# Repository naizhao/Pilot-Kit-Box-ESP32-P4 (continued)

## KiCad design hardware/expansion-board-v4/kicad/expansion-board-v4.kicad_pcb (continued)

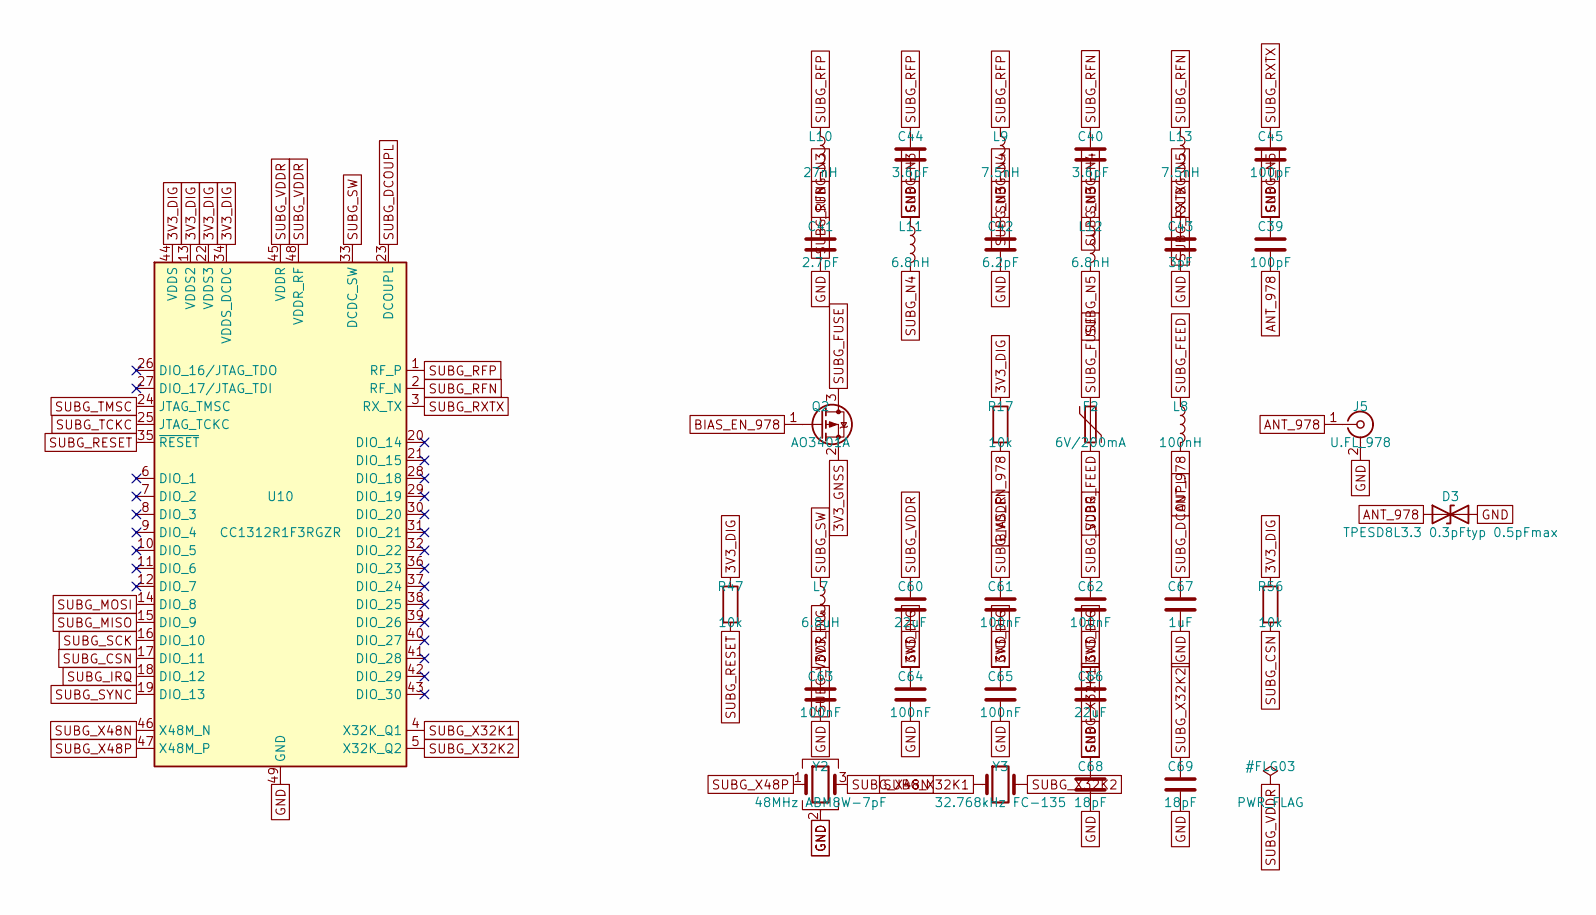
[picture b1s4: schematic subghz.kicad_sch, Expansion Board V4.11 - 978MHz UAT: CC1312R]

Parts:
C39, C45: 100pF; C_0402_1005Metric
C40, C44: 3.6pF; C_0402_1005Metric
C41: 2.7pF; C_0402_1005Metric
C42: 6.2pF; C_0402_1005Metric
C43: 3pF; C_0402_1005Metric
C60, C66: 22uF; C_0805_2012Metric
C61, C62, C63, C64, C65: 100nF; C_0603_1608Metric
C67: 1uF; C_0603_1608Metric
C68, C69: 18pF; C_0603_1608Metric
D3: TPESD8L3.3 0.3pFtyp 0.5pFmax; D_0402_1005Metric
F2: 6V/200mA; Fuse_0805_2012Metric
J5: U.FL_978; U.FL_Hirose_U.FL-R-SMT-1_Vertical
L7: 6.8uH; L_0805_2012Metric
L8: 100nH; L_0402_1005Metric
L9, L13: 7.5nH; L_0402_1005Metric
L10: 27nH; L_0402_1005Metric
L11, L12: 6.8nH; L_0402_1005Metric
Q2: AO3401A; SOT-23
R17, R47, R56: 10k; R_0603_1608Metric
U10: CC1312R1F3RGZR; QFN-48-1EP_7x7mm_P0.5mm_EP5.15x5.15mm
Y2: 48MHz ABM8W-7pF; Crystal_SMD_3225-4Pin_3.2x2.5mm
Y3: 32.768kHz FC-135; Crystal_SMD_3215-2Pin_3.2x1.5mm

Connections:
3V3_DIG: C63.1, C64.1, C65.1, C66.1, R17.1, R47.1, R56.1, U10.13 (VDDS2), U10.22 (VDDS3), U10.34 (VDDS_DCDC), U10.44 (VDDS); also elsewhere on the board
3V3_GNSS: Q2.2 (S); also elsewhere on the board
ANT_978: C39.2, D3.1 (A1), J5.1 (In), L8.2
BIAS_EN_978: Q2.1 (G), R17.2; also elsewhere on the board
GND: C41.2, C42.2, C43.2, C44.2, C45.2, C60.2, C61.2, C62.2, C63.2, C64.2, C65.2, C66.2, C67.2, C68.2, C69.2, D3.2 (A2), J5.2 (Ext), U10.49 (GND), Y2.2 (G), Y2.4 (G); also elsewhere on the board
SUBG_CSN: R56.2, U10.17 (DIO_11); also elsewhere on the board
SUBG_DCOUPL: C67.1, U10.23 (DCOUPL)
SUBG_FEED: F2.2, L8.1
SUBG_FUSE: F2.1, Q2.3 (D)
SUBG_IRQ: U10.18 (DIO_12); also elsewhere on the board
SUBG_MISO: U10.15 (DIO_9); also elsewhere on the board
SUBG_MOSI: U10.14 (DIO_8); also elsewhere on the board
SUBG_N3: C40.2, C41.1, L9.2, L11.1
SUBG_N4: C42.1, L11.2, L12.1
SUBG_N5: C39.1, C43.1, L12.2
SUBG_RESET: R47.2, U10.35 (~RESET); also elsewhere on the board
SUBG_RFN: C40.1, L10.2, L13.1, U10.2 (RF_N)
SUBG_RFP: C44.1, L9.1, L10.1, U10.1 (RF_P)
SUBG_RXTX: C45.1, L13.2, U10.3 (RX_TX)
SUBG_SCK: U10.16 (DIO_10); also elsewhere on the board
SUBG_SW: L7.1, U10.33 (DCDC_SW)
SUBG_SYNC: U10.19 (DIO_13); also elsewhere on the board
SUBG_TCKC: U10.25 (JTAG_TCKC); also elsewhere on the board
SUBG_TMSC: U10.24 (JTAG_TMSC); also elsewhere on the board
SUBG_VDDR: C60.1, C61.1, C62.1, L7.2, U10.45 (VDDR), U10.48 (VDDR_RF)
SUBG_X32K1: C68.1, U10.4 (X32K_Q1), Y3.1
SUBG_X32K2: C69.1, U10.5 (X32K_Q2), Y3.2
SUBG_X48N: U10.46 (X48M_N), Y2.3
SUBG_X48P: U10.47 (X48M_P), Y2.1

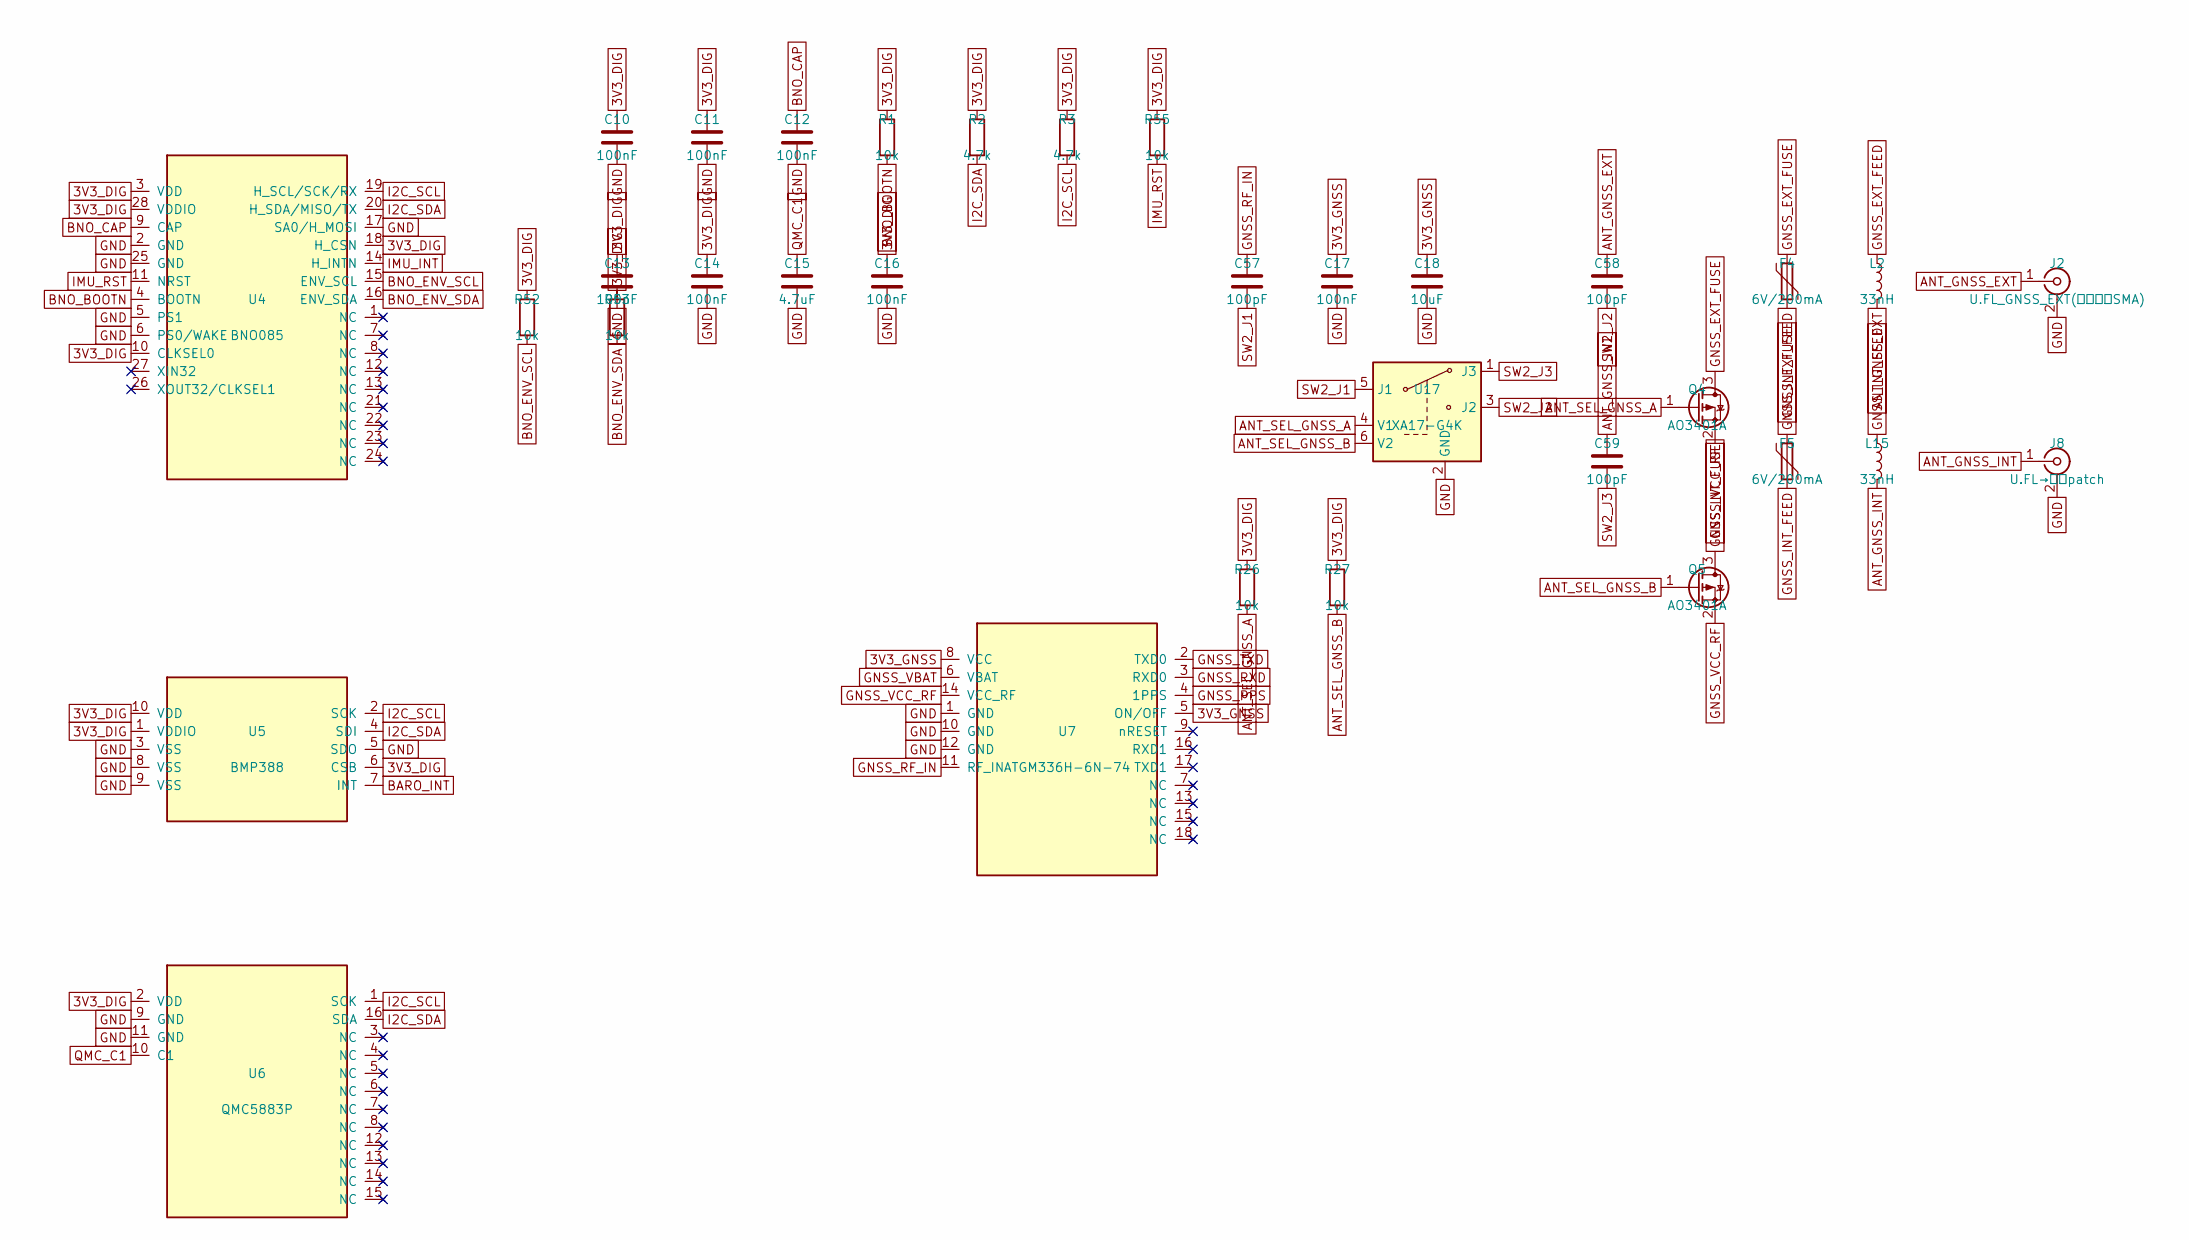
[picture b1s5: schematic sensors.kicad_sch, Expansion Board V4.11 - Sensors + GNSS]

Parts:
C10, C11, C12, C13, C14, C16, C17: 100nF; C_0603_1608Metric
C15: 4.7uF; C_0603_1608Metric
C18: 10uF; C_0805_2012Metric
C57, C58, C59: 100pF; C_0402_1005Metric
F4, F5: 6V/200mA; Fuse_0805_2012Metric
J2: U.FL_GNSS_EXT(经尾线转SMA); U.FL_Hirose_U.FL-R-SMT-1_Vertical
J8: U.FL→内置patch; U.FL_Hirose_U.FL-R-SMT-1_Vertical
L2, L15: 33nH; L_0402_1005Metric
Q4, Q5: AO3401A; SOT-23
R1, R26, R27, R55: 10k; R_0603_1608Metric
R2, R3: 4.7k; R_0603_1608Metric
R52, R53: 10k; R_0402_1005Metric
U4: BNO085; BNO085_LGA-28
U5: BMP388; BMP388_LGA-10
U6: QMC5883P; LGA-16_3x3mm_P0.5mm
U7: ATGM336H-6N-74; ATGM336H_LCC-18
U17: XA17-G4K; SOT-363_SC-70-6

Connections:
3V3_DIG: C10.1, C11.1, C13.1, C14.1, C16.1, R1.1, R2.1, R3.1, R26.1, R27.1, R52.1, R53.1, R55.1, U4.3 (VDD), U4.10 (CLKSEL0), U4.18 (H_CSN), U4.28 (VDDIO), U5.1 (VDDIO), U5.6 (CSB), U5.10 (VDD), U6.2 (VDD); also elsewhere on the board
3V3_GNSS: C17.1, C18.1, U7.5 (ON/OFF), U7.8 (VCC); also elsewhere on the board
ANT_GNSS_EXT: C58.1, J2.1 (In), L2.2
ANT_GNSS_INT: C59.1, J8.1 (In), L15.2
ANT_SEL_GNSS_A: Q4.1 (G), R26.2, U17.4 (V1); also elsewhere on the board
ANT_SEL_GNSS_B: Q5.1 (G), R27.2, U17.6 (V2); also elsewhere on the board
BARO_INT: U5.7 (INT); also elsewhere on the board
BNO_BOOTN: R1.2, U4.4 (BOOTN)
BNO_CAP: C12.1, U4.9 (CAP)
BNO_ENV_SCL: R52.2, U4.15 (ENV_SCL)
BNO_ENV_SDA: R53.2, U4.16 (ENV_SDA)
GND: C10.2, C11.2, C12.2, C13.2, C14.2, C15.2, C16.2, C17.2, C18.2, J2.2 (Ext), J8.2 (Ext), U4.2 (GND), U4.5 (PS1), U4.6 (PS0/WAKE), U4.17 (SA0/H_MOSI), U4.25 (GND), U5.3 (VSS), U5.5 (SDO), U5.8 (VSS), U5.9 (VSS), U6.9 (GND), U6.11 (GND), U7.1 (GND), U7.10 (GND), U7.12 (GND), U17.2 (GND); also elsewhere on the board
GNSS_EXT_FEED: F4.2, L2.1
GNSS_EXT_FUSE: F4.1, Q4.3 (D)
GNSS_INT_FEED: F5.2, L15.1
GNSS_INT_FUSE: F5.1, Q5.3 (D)
GNSS_PPS: U7.4 (1PPS); also elsewhere on the board
GNSS_RF_IN: C57.1, U7.11 (RF_IN)
GNSS_RXD: U7.3 (RXD0); also elsewhere on the board
GNSS_TXD: U7.2 (TXD0); also elsewhere on the board
GNSS_VBAT: U7.6 (VBAT); also elsewhere on the board
GNSS_VCC_RF: Q4.2 (S), Q5.2 (S), U7.14 (VCC_RF)
I2C_SCL: R3.2, U4.19 (H_SCL/SCK/RX), U5.2 (SCK), U6.1 (SCK); also elsewhere on the board
I2C_SDA: R2.2, U4.20 (H_SDA/MISO/TX), U5.4 (SDI), U6.16 (SDA); also elsewhere on the board
IMU_INT: U4.14 (H_INTN); also elsewhere on the board
IMU_RST: R55.2, U4.11 (NRST); also elsewhere on the board
QMC_C1: C15.1, U6.10 (C1)
SW2_J1: C57.2, U17.5 (J1)
SW2_J2: C58.2, U17.3 (J2)
SW2_J3: C59.2, U17.1 (J3)

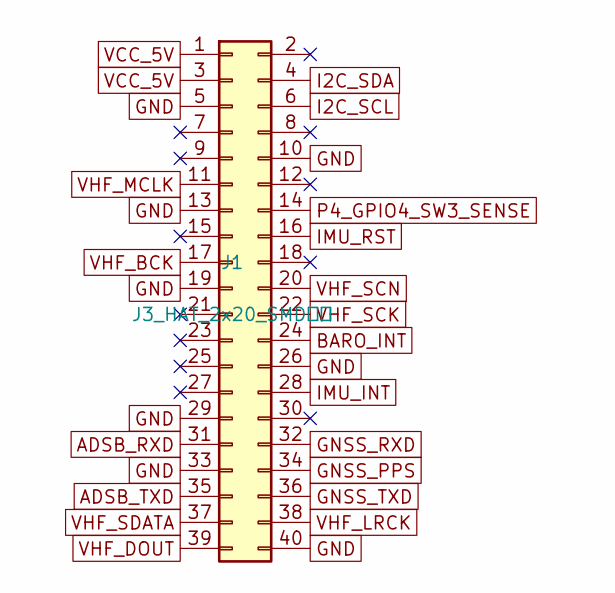
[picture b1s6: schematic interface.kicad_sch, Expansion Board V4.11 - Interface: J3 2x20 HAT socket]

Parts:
J1: J3_HAT_2x20_SMD排针; PinHeader_2x20_P2.54mm_Vertical_SMD

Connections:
ADSB_RXD: J1.31; also elsewhere on the board
ADSB_TXD: J1.35; also elsewhere on the board
BARO_INT: J1.24; also elsewhere on the board
GND: J1.5, J1.10, J1.13, J1.19, J1.26, J1.29, J1.33, J1.40; also elsewhere on the board
GNSS_PPS: J1.34; also elsewhere on the board
GNSS_RXD: J1.32; also elsewhere on the board
GNSS_TXD: J1.36; also elsewhere on the board
I2C_SCL: J1.6; also elsewhere on the board
I2C_SDA: J1.4; also elsewhere on the board
IMU_INT: J1.28; also elsewhere on the board
IMU_RST: J1.16; also elsewhere on the board
P4_GPIO4_SW3_SENSE: J1.14; also elsewhere on the board
VCC_5V: J1.1, J1.3; also elsewhere on the board
VHF_BCK: J1.17; also elsewhere on the board
VHF_DOUT: J1.39; also elsewhere on the board
VHF_LRCK: J1.38; also elsewhere on the board
VHF_MCLK: J1.11; also elsewhere on the board
VHF_SCK: J1.22; also elsewhere on the board
VHF_SCN: J1.20; also elsewhere on the board
VHF_SDATA: J1.37; also elsewhere on the board

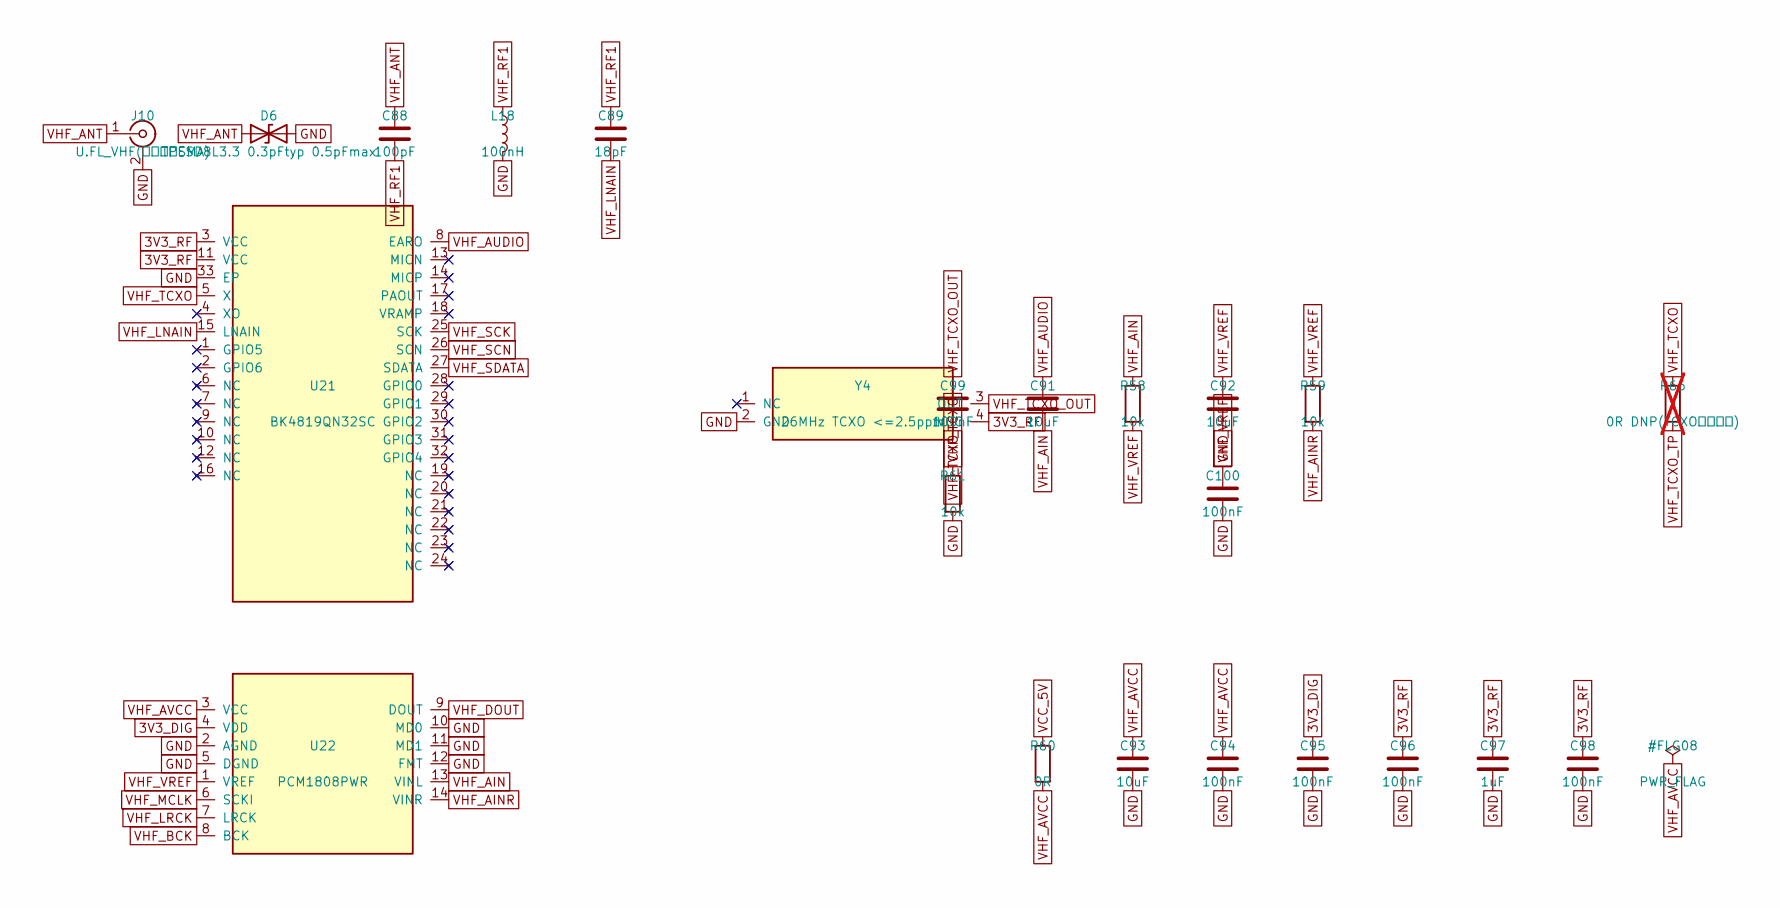
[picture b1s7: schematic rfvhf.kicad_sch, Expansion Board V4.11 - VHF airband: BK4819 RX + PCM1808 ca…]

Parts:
C88: 100pF; C_0603_1608Metric
C89: 18pF; C_0603_1608Metric
C91, C92, C93: 10uF; C_0805_2012Metric
C94, C95, C96, C98, C100: 100nF; C_0603_1608Metric
C97: 1uF; C_0603_1608Metric
C99: 100nF; C_0402_1005Metric
D6: TPESD8L3.3 0.3pFtyp 0.5pFmax; D_0402_1005Metric
J10: U.FL_VHF(经尾线转SMA); U.FL_Hirose_U.FL-R-SMT-1_Vertical
L18: 100nH; L_0402_1005Metric
R58, R59: 10k; R_0603_1608Metric
R60: 0R; R_0603_1608Metric
R61: 10k; R_0402_1005Metric
R66: 0R DNP(TCXO探测隔离); R_0603_1608Metric; not fitted
U21: BK4819QN32SC; QFN-32-1EP_4x4mm_P0.4mm_EP2.65x2.65mm
U22: PCM1808PWR; TSSOP-14_4.4x5mm_P0.65mm
Y4: 26MHz TCXO <=2.5ppm; Crystal_SMD_2520-4Pin_2.5x2.0mm

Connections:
3V3_DIG: C95.1, U22.4 (VDD); also elsewhere on the board
3V3_RF: C96.1, C97.1, C98.1, U21.3 (VCC), U21.11 (VCC), Y4.4 (VCC); also elsewhere on the board
GND: C92.2, C93.2, C94.2, C95.2, C96.2, C97.2, C98.2, C100.2, D6.2 (A2), J10.2 (Ext), L18.2, R61.2, U21.33 (EP), U22.2 (AGND), U22.5 (DGND), U22.10 (MD0), U22.11 (MD1), U22.12 (FMT), Y4.2 (GND); also elsewhere on the board
VCC_5V: R60.1; also elsewhere on the board
VHF_AIN: C91.2, R58.1, U22.13 (VINL)
VHF_AINR: R59.2, U22.14 (VINR)
VHF_ANT: C88.1, D6.1 (A1), J10.1 (In)
VHF_AUDIO: C91.1, U21.8 (EARO); also elsewhere on the board
VHF_AVCC: C93.1, C94.1, R60.2, U22.3 (VCC)
VHF_BCK: U22.8 (BCK); also elsewhere on the board
VHF_DOUT: U22.9 (DOUT); also elsewhere on the board
VHF_LNAIN: C89.2, U21.15 (LNAIN)
VHF_LRCK: U22.7 (LRCK); also elsewhere on the board
VHF_MCLK: U22.6 (SCKI); also elsewhere on the board
VHF_RF1: C88.2, C89.1, L18.1
VHF_SCK: U21.25 (SCK); also elsewhere on the board
VHF_SCN: U21.26 (SCN); also elsewhere on the board
VHF_SDATA: U21.27 (SDATA); also elsewhere on the board
VHF_TCXO: C99.2, R61.1, R66.1, U21.5 (XI)
VHF_TCXO_OUT: C99.1, Y4.3 (OUT)
VHF_TCXO_TP: R66.2; also elsewhere on the board
VHF_VREF: C92.1, C100.1, R58.2, R59.1, U22.1 (VREF)

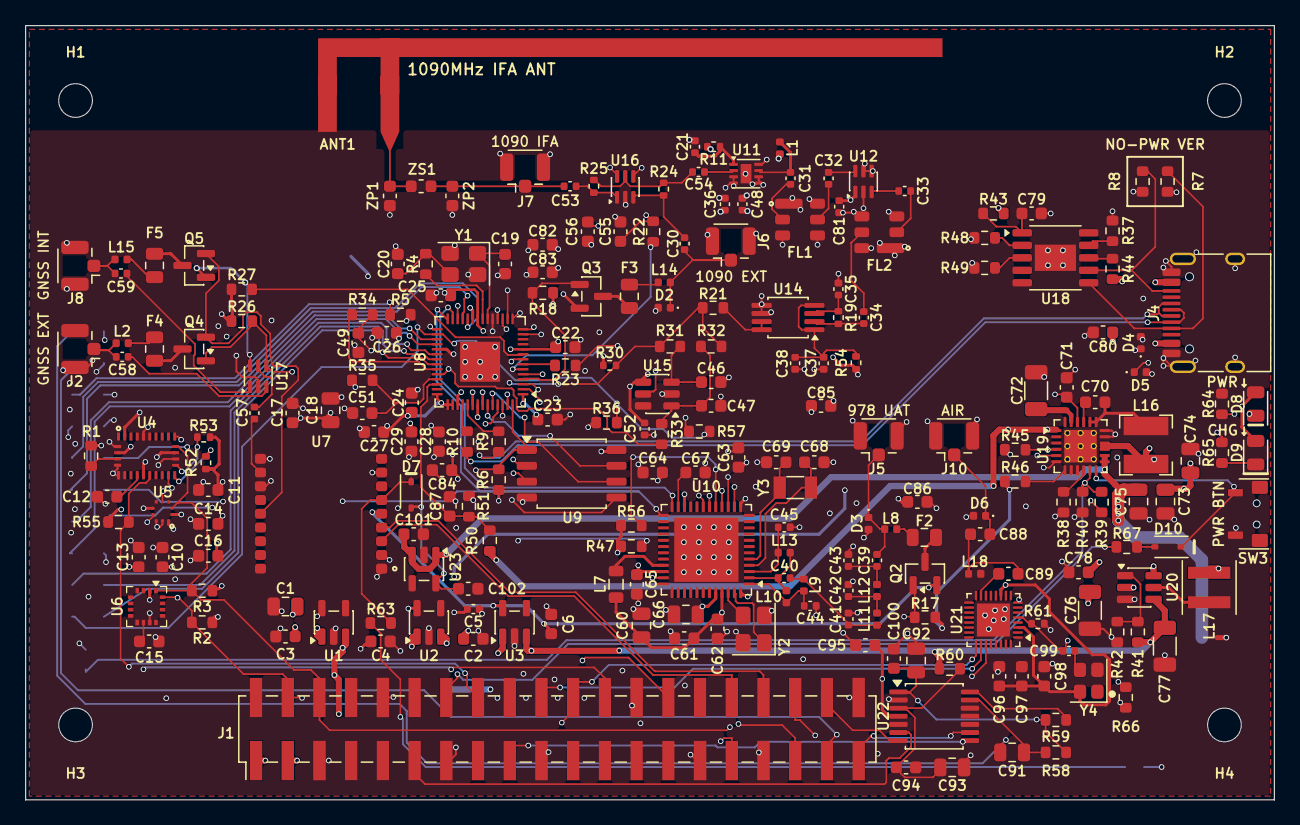
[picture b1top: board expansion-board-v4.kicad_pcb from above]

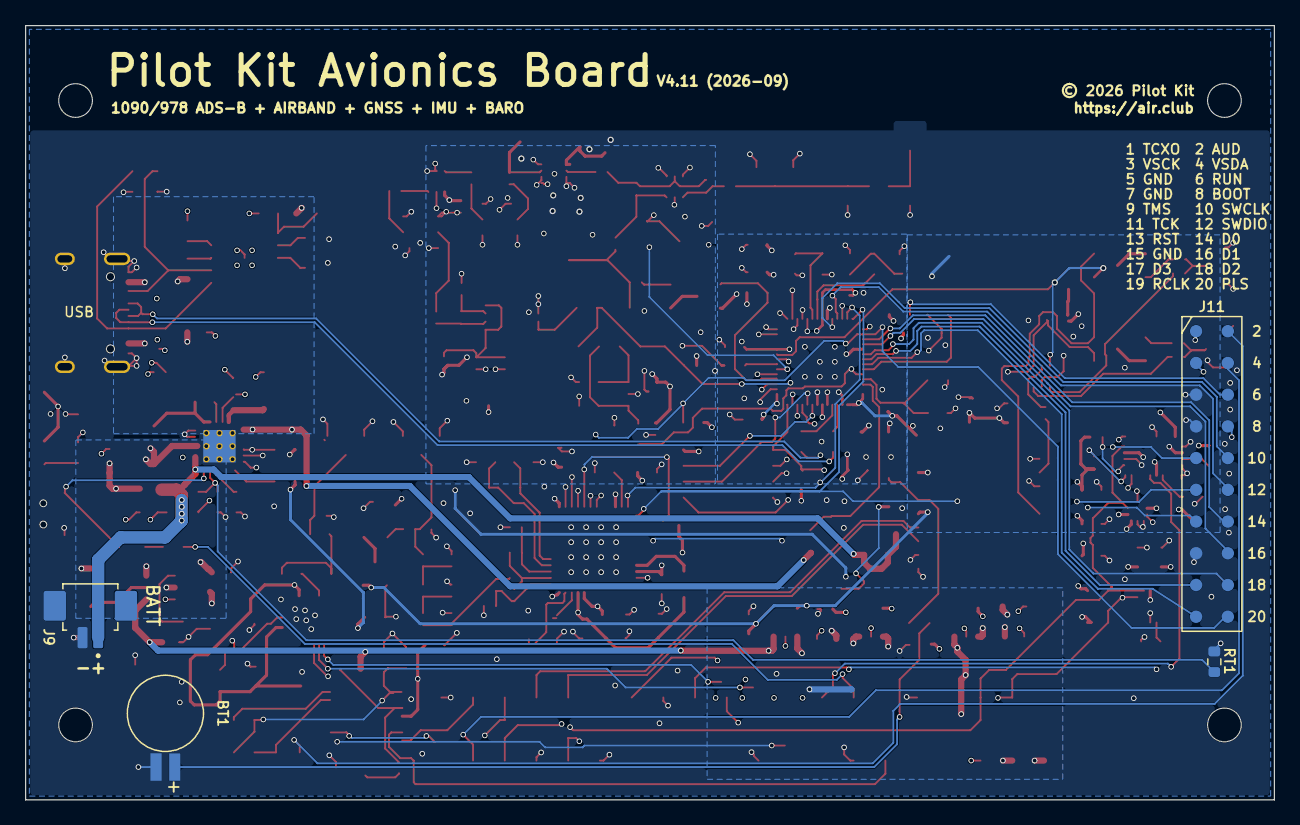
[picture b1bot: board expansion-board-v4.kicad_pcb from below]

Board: 6 copper layers, 100.0 x 62.0 mm, 235 parts (4 on the bottom side), 162 nets.

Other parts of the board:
H1, H2, H3, H4: MountingHole_2.7mm_M2.5

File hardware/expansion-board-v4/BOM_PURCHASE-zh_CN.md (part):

# V4.11 采购清单（唯一权威版，从网表自动导出——不要手改）

> ⚠️ **本文件取代此前散落在设计文档 §7/§12/§13 的所有采购表格。**

> 网表变更后重跑 `gen_bom.py` 即可；脚本带断言，任何未归类的元件都会报错，不会漏项。

> **IFA**：50.0mm铜箔外包络（48.5mm中心线）已按V4.0实板装盒VNA结果定型；默认0R/DNP为本次实测直通状态。


共 231 个元件 / 106 个料号。


**库类型**：`基础✅` 免 ¥20 上机费且损耗由嘉立创承担；`扩展⚠️` 每种 ¥20（当前靠券减免，券没了就是真金白银）。本轮在用的扩展库料共 **27 种**，下次优化优先从这些里找基础库替代。`按值配料` 表示没指定料号，库类型由嘉立创匹配页当场决定——那些也要在匹配时留意。


| 采购 | 类别 | 值/规格 | 封装 | 数量 | 位号 | 推荐型号 | 立创料号 | 库 | 说明 |
|---|---|---|---|---|---|---|---|---|---|
| 🔴必买指定 | 二极管 | 1N4148WS | D_SOD-323 | 2 | D10,D7 | 1N4148WS | C2128 | ? | 3V3_BKP → GNSS_VBAT 隔离：挡住主电池放空后电池经 LDO 输出倒灌回输入（TPS7A20 手册明确会损坏器件）；基础库 |
| 🔴必买指定 | 低电容ESD | TPESD8L3.3 0.3pFtyp 0.5pFmax | D_0402_1005Metric | 5 | D2,D3,D4,D5,D6 | TECH PUBLIC TPESD8L3.3CT5G | C2830293 | 扩展⚠️ | D2/D3 天线口 + D4/D5 USB D+/D−，同一料号。Cj 0.3pF typ / 0.5pF max（TPESD8L3.3_OCR.pdf 实测表）；普通 5V ESD 管 Cj 20-50pF 会直接吃掉射频信号。双向、无极性 |
| 🔴必买指定 | 备份电池 | MS621FE-FL11E(选贴) | MS621FE-FL11E | 1 | BT1 | Seiko MS621FE-FL11E | 淘宝（嘉立创无此料） | ? | 3V 可充电锂锰 5.5mAh φ6.8×2.1 焊接式；⚠️只能用 ML/MS 体系，LIR 满电 4.2V 会超 GNSS VBAT 的 3.6V 极限。封装自建（官方 FL11E 焊脚中心距 2.5mm，KiCad 官方库那个是 1.5mm，对不上）。手焊，不进 SMT |
| 🔴必买指定 | 射频-978匹配 | 2.7pF | C_0402_1005Metric | 1 | C41 | 风华 0402CG2R7C500NT（C0G） | C1561 | 扩展⚠️ | ⚠️必须 C0G |
| 🔴必买指定 | 射频-978匹配 | 27nH | L_0402_1005Metric | 1 | L10 | muRata LQW15AN27NH00D（绕线 ±3% SRF3.5G） | C113111 | 扩展⚠️ | 备选 Sunltech SCW1005C27NJST C330864（±5% SRF3.5G 库存8872）、APV AHW1005C-27NJTF C6364690（±5% SRF2.48G） |
| 🔴必买指定 | 射频-978匹配 | 3.6pF | C_0402_1005Metric | 2 | C40,C44 | YAGEO AC0402CRNPO9BN3R6（C0G） | C5552081 | 扩展⚠️ | ⚠️必须 C0G/NP0，X7R 调不准匹配 |
| 🔴必买指定 | 射频-978匹配 | 6.2pF | C_0402_1005Metric | 1 | C42 | 风华 0402CG6R2C500NT（C0G） | C41744 | 扩展⚠️ | ⚠️必须 C0G |
| 🔴必买指定 | 射频-978匹配 | 6.8nH | L_0402_1005Metric | 2 | L11,L12 | muRata LQW15AN6N8G00D（绕线高Q） | C82919 | 扩展⚠️ | 国产替代 Sunltech SCW1005C6N8JST C330847 |
| 🔴必买指定 | 射频-978匹配 | 7.5nH | L_0402_1005Metric | 2 | L13,L9 | muRata LQW15AN7N5G00D（绕线高Q） | C82918 | 扩展⚠️ | 国产替代 Sunltech SCW1005C7N5JST C330848 |
| 🔴必买指定 | 射频-LNA偏置 | 3.32k | R_0402_1005Metric | 1 | R11 | 0402 3.32k ±1% | — | 按值配料 | QPL9547 pin1 Vbias；按原厂评估板值，禁止用 0Ω 直连 3V3_RF |
| 🔴必买指定 | 射频-LNA去耦 | 470pF C0G | C_0402_1005Metric | 1 | C81 | 0402 470pF C0G/NP0 ±5% | — | 按值配料 | BGA2817 pin1 专属 Cdec；贴近 U12，替代料必须锁 C0G/NP0 |
| 🔴必买指定 | 射频-LNA馈电扼流 | 18nH 0402CS-18NXGRW | L_0402_1005Metric | 1 | L1 | Coilcraft 0402CS-18NXGRW 或同等高 SRF 绕线 18nH | — | 按值配料 | QPL9547 pin7 漏极馈电；按原厂评估板 18nH，替代料必须核对 1090MHz 时仍为感性 |
| 🔴必买指定 | 射频-偏置扼流 | 100nH | L_0402_1005Metric | 3 | L14,L18,L8 | DDY WI0402IFR10KST-HF（绕线） | C18221115 | 扩展⚠️ | ⚠️SRF 1.4GHz。常见的叠层款 SRF 仅 600-700MHz，在 1090MHz 已变电容会把射频短到电源 |
| 🔴必买指定 | 射频-偏置扼流 | 33nH | L_0402_1005Metric | 2 | L15,L2 | APV AHW1005C-33NJTF（绕线） | C6807986 | 扩展⚠️ | ⚠️SRF 2.35GHz。GNSS 1575MHz 要求 SRF≥2GHz，叠层款不合格 |
| 🔴必买指定 | 射频-检波耦合 | 3pF | C_0402_1005Metric | 1 | C43 | 三环 TCC0402COG3R0C500AT（C0G） | C696883 | 扩展⚠️ | ⚠️必须 C0G |
| 🔴必买指定 | 射频-端接 | 52.3R | R_0402_1005Metric | 1 | R19 | YAGEO RC0402FR-0752R3L ±1% | C273696 | 扩展⚠️ | 必须 ±1%，不可用 51R±5% 代 |
| 🔴必买指定 | 射频-耦合/旁路 | 100pF C0G | C_0402_1005Metric | 5 | C31,C32,C33,C34,C35 | 风华 0402CG101J500NT（C0G） | C1546 | 基础✅ | C34/C35 决定 1090MHz 检波输入高通，必须锁 C0G/NP0 |
| 🔴必买指定 | 晶振 | 12MHz CL=10pF ABM8-272-T3 | Crystal_SMD_3225-4Pin_3.2x2.5mm | 1 | Y1 | Abracon ABM8-12.000MHZ-10-1-U-T3 / ABM8-272-T3 | — | 按值配料 | RP2040 主晶振，必须 CL=10pF；配 C19/C20=15pF C0G。🔴 别换成嘉立创基础库那颗 3225 的 12MHz（2026-09-04 在线核实）：封装一样、频率一样，但负载电容是本值的两倍，配上去频率会偏，而 USB 只容 ±2500ppm。换晶振必须连 C19/C20 一起重算 |
| 🔴必买指定 | 晶振负载 | 15pF C0G | C_0603_1608Metric | 2 | C19,C20 | 三星 CL10C150JB8NNNC（C0G） | C1644 | 基础✅ | 配 ABM8-272-T3(CL=10pF)，C19/C20 必须同值 |
| 🔴必买指定 | 电源-PD | CH224K | CH224K_ESSOP-10 | 1 | U18 | CH224K | C970725 | 扩展⚠️ | PD 诱骗 9V；4-22V 输入 |
| 🔴必买指定 | 电源-充电 | SY6970 | QFN-24-1EP_4x4mm_P0.5mm_EP2.6x2.6mm_ThermalVias | 1 | U19 | SY6970QCC | C5357542 | ? | 5A 充电 + I2C 电量计，1.5MHz |
| 🔴必买指定 | 电源-升压 | SY7069 | TSOT-23-6 | 1 | U20 | SY7069ADC | 淘宝（立创未见） | ? | 同步升压 5V，I_LIM 3.0A |
| 🔴必买指定 | 电源-升压电感 | 4.7uH XEL4030-472MEC | L_Coilcraft_XxL4030 | 1 | L17 | Coilcraft XEL4030-472MEC | — | 按值配料 | SY7069 功率电感；替代料必须复核 Isat、Irms、DCR、温升和封装 |
| 🔴必买指定 | 电源-电容 | 22uF 16V X5R | C_1206_3216Metric | 1 | C77 | 1206 22uF 16V X5R/X7R | — | 按值配料 | SY7069 输出储能；必须标 16V，并核对 5V DC bias 下有效容值 |
| 🔴必买指定 | 电源-电感 | 1uH | L_Bourns-SRN4018 | 1 | L16 | 1uH SRN4018 Isat>=5A | — | 按值配料 | SY6970 开关电感，配 1.5MHz |
| 🔴必买指定 | 连接器 | MX1.25WT-2P BAT | MX1.25WT-2P_1x02-1MP_P1.25mm_Horizontal | 1 | J9 | MX1.25 卧贴 1.25WT-2P | — | 按值配料 | 电池座；MP 1.8x2.4/外缘距 7.50，与 PicoBlade 不通用 |
| 🟡有推荐 | CC1312R DCDC | 6.8uH | L_0805_2012Metric | 1 | L7 | TDK MLZ2012N6R8LT000 | C82157 | 扩展⚠️ | ⚠️全站 0805 里只有它 DCR<300mΩ 且 Isat≥100mA（250mΩ/110mA，刚压线） |
| 🟡有推荐 | PD输入储能 | 1uF 25V | C_0603_1608Metric | 1 | C80 | SAMSUNG CL10A105KB8NNNC | C15849 | 基础✅ | C80 挂 USB_VBUS；PD 诱骗后是 9V，耐压必须 ≥25V。基础库，2 片总成本 ¥0.14，库存千万级 |
| 🟡有推荐 | PMOS 高边开关 | AO3401A | SOT-23 | 4 | Q2,Q3,Q4,Q5 | AOS AO3401A（原厂，基础库） | C15127 | ? | **嘉立创基础库**：损耗0/最小贴装0，买 8 颗就够，免 ¥20 上机费。有券时 UMW C347476 的料费更低（¥2.04 vs ¥4.77） |
| 🟡有推荐 | U.FL 座 | U.FL_1090_EXT(经尾线转SMA) | U.FL_Hirose_U.FL-R-SMT-1_Vertical | 1 | J6 | 聚兴泰 AIPEX-1 | C41432122 | 扩展⚠️ | IPEX1 板端内针 50Ω / DC~6GHz / VSWR1.3。**规格书标注 3 PADS TYPE**，焊盘与板上 U.FL_Hirose_U.FL-R-SMT-1_Vertical 完全匹配（跨距4.00/间距1.90/2.20×1.05）。4 个：1090外接/978/GNSS外接/GNSS内置patch。外接的两个另配 U.FL→SMA 尾线。⚠️ 换牌子必须核对焊盘数——四焊盘款（如品赞 C5299419）会多一脚悬空 |
| 🟡有推荐 | U.FL 座 | U.FL_978 | U.FL_Hirose_U.FL-R-SMT-1_Vertical | 1 | J5 | 聚兴泰 AIPEX-1 | C41432122 | 扩展⚠️ | IPEX1 板端内针 50Ω / DC~6GHz / VSWR1.3。**规格书标注 3 PADS TYPE**，焊盘与板上 U.FL_Hirose_U.FL-R-SMT-1_Vertical 完全匹配（跨距4.00/间距1.90/2.20×1.05）。4 个：1090外接/978/GNSS外接/GNSS内置patch。外接的两个另配 U.FL→SMA 尾线。⚠️ 换牌子必须核对焊盘数——四焊盘款（如品赞 C5299419）会多一脚悬空 |
| 🟡有推荐 | U.FL 座 | U.FL_GNSS_EXT(经尾线转SMA) | U.FL_Hirose_U.FL-R-SMT-1_Vertical | 1 | J2 | 聚兴泰 AIPEX-1 | C41432122 | 扩展⚠️ | IPEX1 板端内针 50Ω / DC~6GHz / VSWR1.3。**规格书标注 3 PADS TYPE**，焊盘与板上 U.FL_Hirose_U.FL-R-SMT-1_Vertical 完全匹配（跨距4.00/间距1.90/2.20×1.05）。4 个：1090外接/978/GNSS外接/GNSS内置patch。外接的两个另配 U.FL→SMA 尾线。⚠️ 换牌子必须核对焊盘数——四焊盘款（如品赞 C5299419）会多一脚悬空 |
| 🟡有推荐 | U.FL 座 | U.FL_IFA_TEST(π后调试口) | U.FL_Hirose_U.FL-R-SMT-1_Vertical | 1 | J7 | 聚兴泰 AIPEX-1 | C41432122 | 扩展⚠️ | IPEX1 板端内针 50Ω / DC~6GHz / VSWR1.3。**规格书标注 3 PADS TYPE**，焊盘与板上 U.FL_Hirose_U.FL-R-SMT-1_Vertical 完全匹配（跨距4.00/间距1.90/2.20×1.05）。4 个：1090外接/978/GNSS外接/GNSS内置patch。外接的两个另配 U.FL→SMA 尾线。⚠️ 换牌子必须核对焊盘数——四焊盘款（如品赞 C5299419）会多一脚悬空 |
| 🟡有推荐 | U.FL 座 | U.FL_VHF(经尾线转SMA) | U.FL_Hirose_U.FL-R-SMT-1_Vertical | 1 | J10 | 聚兴泰 AIPEX-1 | C41432122 | 扩展⚠️ | IPEX1 板端内针 50Ω / DC~6GHz / VSWR1.3。**规格书标注 3 PADS TYPE**，焊盘与板上 U.FL_Hirose_U.FL-R-SMT-1_Vertical 完全匹配（跨距4.00/间距1.90/2.20×1.05）。4 个：1090外接/978/GNSS外接/GNSS内置patch。外接的两个另配 U.FL→SMA 尾线。⚠️ 换牌子必须核对焊盘数——四焊盘款（如品赞 C5299419）会多一脚悬空 |
| 🟡有推荐 | U.FL 座 | U.FL→内置patch | U.FL_Hirose_U.FL-R-SMT-1_Vertical | 1 | J8 | 聚兴泰 AIPEX-1 | C41432122 | 扩展⚠️ | IPEX1 板端内针 50Ω / DC~6GHz / VSWR1.3。**规格书标注 3 PADS TYPE**，焊盘与板上 U.FL_Hirose_U.FL-R-SMT-1_Vertical 完全匹配（跨距4.00/间距1.90/2.20×1.05）。4 个：1090外接/978/GNSS外接/GNSS内置patch。外接的两个另配 U.FL→SMA 尾线。⚠️ 换牌子必须核对焊盘数——四焊盘款（如品赞 C5299419）会多一脚悬空 |
| 🟡有推荐 | USB VBUS分压 | 30k | R_0603_1608Metric | 1 | R50 | UNI-ROYAL 0603WAF3002T5E | C22984 | 基础✅ | R50 上臂。基础库，2 片总成本 ¥0.07；R51 下臂 10k 用现有元件本 |
| 🟡有推荐 | USB-C | USB-C_16P | USB_C_Receptacle_HRO_TYPE-C-31-M-12 | 1 | J4 | HRO TYPE-C-31-M-12 | — | 按值配料 | RP2040 刷机口 |
| 🟡有推荐 | VBUS分压滤波 | 10nF C0G | C_0603_1608Metric | 1 | C87 | 0603 10nF C0G/NP0 25V以上 | — | 按值配料 | C87，USB_VBUS_SENSE 对地。**自己贴**：C0G 仅扩展库有，1 颗不值 ¥20 上机费。🔴 反例：基础库 C57112 是 **X7R**（2026-09-04 在线核实），别拿它换 |
| 🟡有推荐 | 储能 | 22uF | C_0805_2012Metric | 2 | C60,C66 | Samsung CL21A226MAQNNNE（基础库） | C45783 | ? | 25V ±20% X5R。**嘉立创基础库**，免 ¥20 上机费。25V 比原设计的 16V 更高，向上兼容；±20% 对储能电容够用（X5R 在直流偏压下本就掉一半容值） |
| 🟡有推荐 | 去耦 | 100nF | C_0603_1608Metric | 28 | C10,C100,C11,C12,C13,C14…(28) | 国巨 CC0603KRX7R9BB104（基础库） | C14663 | ? | **嘉立创基础库**，买 38 颗免上机费。有券时 Venkel C3834556 料费更低（¥1.79 vs ¥3.08） |
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
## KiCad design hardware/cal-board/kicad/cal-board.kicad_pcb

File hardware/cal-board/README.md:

# VNA 校准 / 转接板（2 层 · 华秋免费打样档）

一块给 NanoVNA 用的板载 SOL 校准件 + U.FL/SMA 转接板。

    生成：~/Applications/KiCad/KiCad.app/Contents/Frameworks/Python.framework/Versions/Current/bin/python3 tools/gen_cal_board.py
    产物：kicad/cal-board.kicad_pcb        95 × 92 mm，2 层，1.6mm

## 为什么要做它

U.FL 没有现成的 SOL 校准件，校准面只能停在 VNA 的 SMA 口，**尾线（pigtail）
留在测量链路里**。2026-09-04 实测：V4.4 板 J6 读到 11.45pF，理论只有 1.6pF，
差 7 倍，一度以为板子坏了 —— 实际是尾线没被校准掉。

尾线对读数做**两件**事，只记住第一件就会误判：

| | 后果 |
|---|---|
| **相位旋转** | R/X 重新分配，X 过零的频率被挪动 |
| **损耗衰减** | \|Γ\| 被拉向圆心，**SWR 被压得偏乐观** |

同一根尾线（往返 0.55dB）：天线（|Γ|=0.04）SWR 1.083→1.089 可忽略；
开路线（|Γ|=0.885）SWR 10.84→**16.40**，压低了三分之一。

有了这块板，就能把尾线**真正校准进 VNA**，而不是事后补偿。
（软件补偿仍可用：`hardware/tools/vna_deembed.py`，只需一次尾线空接读数。）

## 板上有什么

```
┌─ 1) U.FL SOL ─────────────────────┬─ 3) THRU / adapters ─┐
│  J1 OPEN   J2 SHORT   J3 LOAD     │  J7─J8  UFL-SMA 7.5mm│
├─ 2) SMA SOL ──────────────────────┴──────────────────────┤
│  J4 OPEN   J5 SHORT   J6 LOAD                            │
│  J9─J10 UFL-UFL 3.5mm      J11─J12 SMA-SMA 14.0mm        │
└──────────────────────────────────────────────────────────┘
```

| 区 | 用途 |
|---|---|
| **① U.FL SOL** | **核心**。校准 `SMA母–IPEX` 这类尾线，校准面落在 U.FL 接触面上，与实际插 J6/J7 时完全一致 |
| **② SMA SOL** | 校准 `SMA母–SMA母` 尾线。**如果 NanoVNA 自带 SMA 校准件，这三组可以不焊** |
| **③ THRU / 转接** | U.FL↔SMA 转接、S21 归一化、验证线缆损耗 |

## 设计上的三个硬约束

**① 参考面必须一致 —— 这是校准板的命根子。**
Short/Open/Load 到连接器焊盘的距离必须相同，否则三者不在同一参考面，
解出来的误差模型是错的。本板做法是**零长度**：标准件直接贴在信号焊盘边上。

    OPEN   信号焊盘悬空（只有焊盘自身的边缘电容）
    SHORT  紧邻打 3 个过孔到底层地（多孔并联压低短路电感）
    LOAD   紧邻贴 2×100Ω 0402 并联（并联把寄生电感减半）

**② 走线长度分两档处理。**
1090MHz 在这个叠层上的波导波长是 150.4mm，**λ/20 = 7.5mm** 是分界：

| 组 | 走线 | 线宽 | 依据 |
|---|---|---|---|
| UFL-UFL | 3.45mm | 1.20mm | 电长度不足 9°，阻抗偏差可忽略 |
| UFL-SMA | 7.47mm | 1.20mm | 刚好卡进 λ/20 |
| SMA-SMA | 14.0mm | **2.40mm** | 超过 λ/20，须按 50Ω 走 |

⚠️ 2 层 1.6mm 板的 50Ω 线宽是 **2.692mm**（由嘉立创 2 层官方数据点
h=1.43/W=2.6916/50Ω 反标定 Dk=4.423 算得）。但 **SMA 垂直座四个地脚之间
只有 2.83mm 净空**，留 0.2mm 间距后最宽只能走 **2.43mm**。取 2.40mm（53.0Ω）
是这个几何硬限与阻抗之间的折中，不是随手写的数。

**③ 走线端点不能落在 U.FL 焊盘中心。**
U.FL 封装自带 `top_keepout` 规则区，其右边界离信号焊盘中心只有 0.535mm，
而走线端帽是圆的（半径 = 线宽/2）会伸进去。端点内缩 0.35mm，
既仍与焊盘重叠导通，又让端帽退出禁布区。

## 元件

| 位号 | 件 | 数量 | 备注 |
|---|---|---|---|
| J1–J3, J7, J9, J10 | U.FL 座 Hirose U.FL-R-SMT-1 | 6 | 与主板 J2/J5–J8 同款 |
| J4–J6, J8, J11, J12 | SMA 垂直四脚方法兰 | 6 | Amphenol 132134 兼容封装 |
| R1–R4 | 0402 100Ω ±1% | 4 | 每个 LOAD 用 2 个并联 = 50Ω |

⚠️ **没有采用那款「外螺内孔·偏脚·间距 1.7mm」板边座**：它的地脚间距与 KiCad
现成的 `SMA_Amphenol_132289_EdgeMount`（±4.25mm）对不上，仅凭商品图自制封装会
踩「换料必查焊盘图」那个坑。要加这款，需要先拿到**规格书或实测**法兰尺寸 /
脚宽 / 脚长 / 中心针直径。四脚方法兰款货源足、封装确定，先用它。

## 怎么用

**校准 U.FL 尾线**（把尾线纳入校准面）：

1. VNA 设好频段（如 950–1200MHz）
2. 尾线 SMA 端接 VNA PORT1，U.FL 端依次插 **J1(OPEN) → J2(SHORT) → J3(LOAD)**
3. 每插一个，在 NanoVNA 的 CAL 菜单里点对应项，最后 DONE + SAVE
4. 之后直接插主板的 J6/J7，读数就是板上真实值，**不用再 de-embed**

**验证**：校准后插 J1(OPEN)，Smith 图应落在最右（开路）；插 J2 落最左（短路）；
插 J3 落圆心（50Ω）。三者都对，校准才算成功。

## 已知误差源（不追求实验室级精度时可忽略）

自制标准件的寄生量未知，NanoVNA 会按理想件处理，因此存在残余误差：

| | 量级 @1090MHz | 影响 |
|---|---|---|
| OPEN 的焊盘边缘电容 | ~0.1pF → −j1460Ω | 相对理想开路（∞）偏一点 |
| SHORT 的过孔电感 | 3 孔并联约 0.3nH → +j2Ω | 相对理想短路（0Ω）偏一点 |
| LOAD 的电阻寄生 | 2×100Ω 并联后约 0.2nH | 高频略偏感性 |

对 1090MHz 单频点的用途足够。要更准就得买带 ADAPTER 定义的商用校准件。

## 制造

    2 层 · 1.6mm · 1oz · 绿油白字 · 最小线宽 1.20mm · 最小孔径 0.4mm
    尺寸 95 × 92mm（华秋免费档 10×10cm 以内）

工艺余量很大（最小线宽 1.2mm 远超 5/5mil 档），任何板厂的免费档都能做。

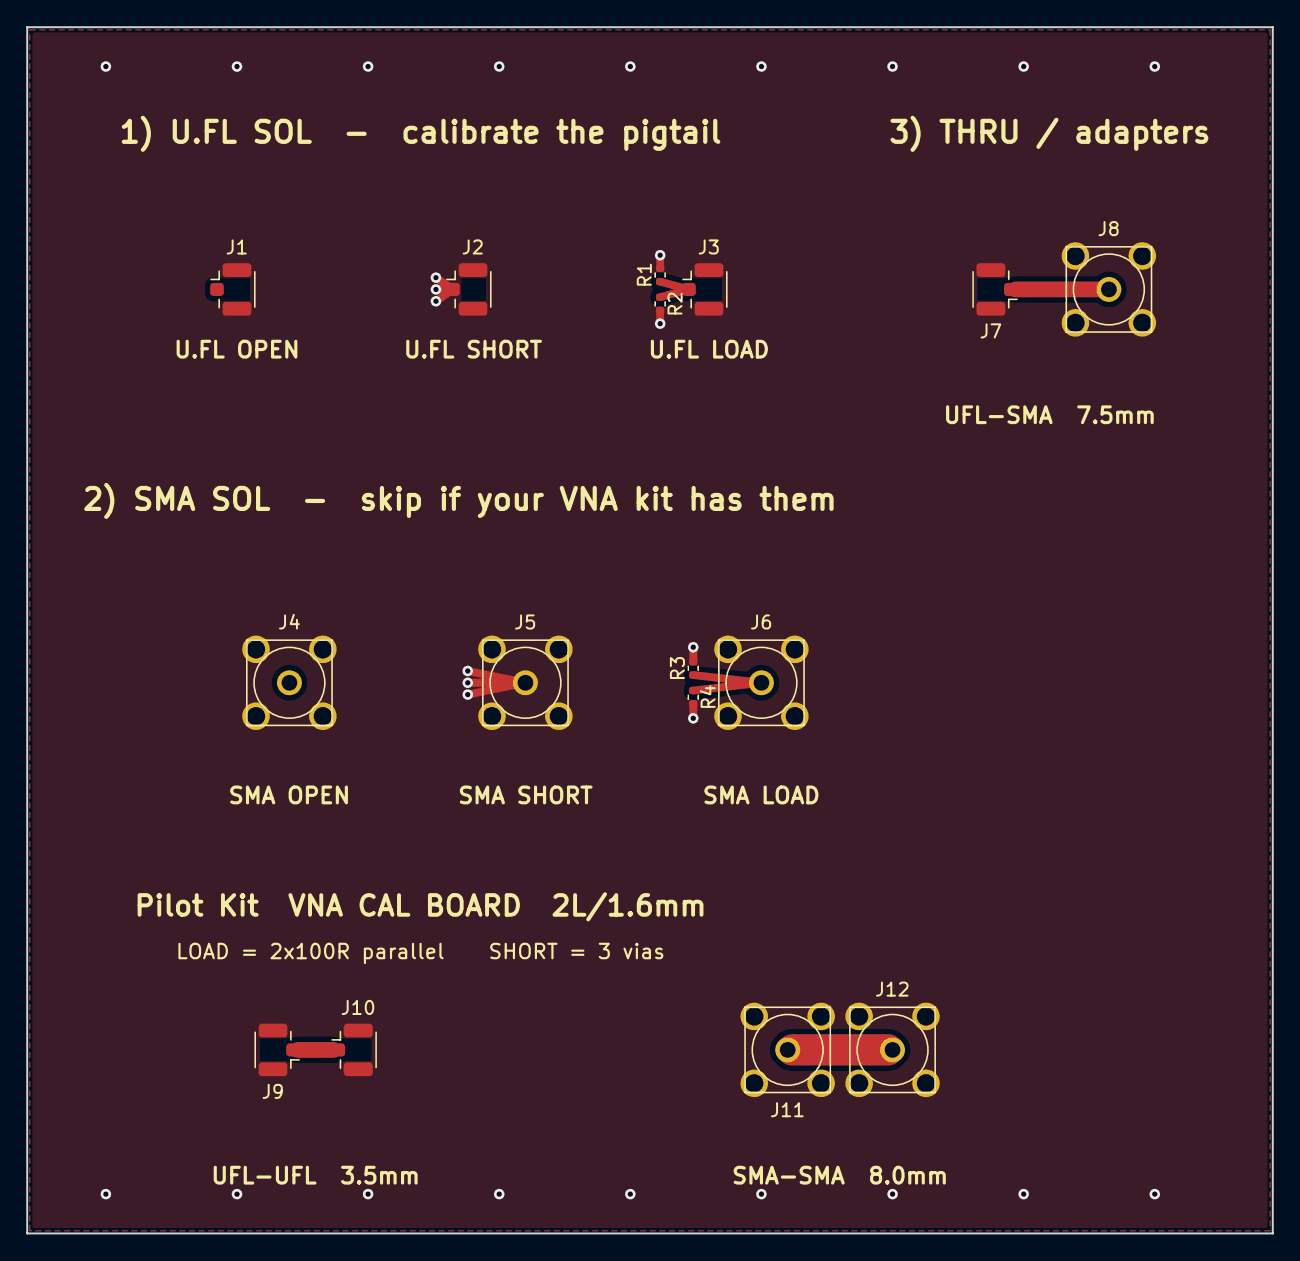
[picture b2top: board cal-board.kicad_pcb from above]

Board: 2 copper layers, 95.0 x 92.0 mm, 16 parts (0 on the bottom side), 6 nets.

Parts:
J1, J2, J3, J7, J9, J10: U.FL_Hirose_U.FL-R-SMT-1_Vertical
J4, J5, J6, J8, J11, J12: SMA_KHD; SMA_KHD_Vertical_THT
R1, R2, R3, R4: 100; R_0402_1005Metric

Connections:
GND: J1.2, J2.1, J2.2, J3.2, J4.2, J5.1, J5.2, J6.2, J7.2, J8.2, J9.2, J10.2, J11.2, J12.2, R1.2, R2.2, R3.2, R4.2
SMA_LOAD: J6.1, R3.1, R4.1
THRU_SMA-SMA: J11.1, J12.1
THRU_UFL-SMA: J7.1, J8.1
THRU_UFL-UFL: J9.1, J10.1
UFL_LOAD: J3.1, R1.1, R2.1

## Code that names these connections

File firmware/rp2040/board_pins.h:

/*
 * board_pins.h — RP2040 唯一 pin 清单。
 * 来源：hardware/expansion-board-v4/PINMAP.md §2（v3/v4 同源）。
 * 改任何一个脚都要先改 PINMAP，再改这里——顺序不能反。
 */
#pragma once

#define PIN_P4_UART_TX    0   /* UART0 TX → P4 GPIO46（J3-35）*/
#define PIN_P4_UART_RX    1   /* UART0 RX ← P4 GPIO32（J3-31）*/
#define PIN_BIAS_EN_1090  2   /* bias tee PMOS gate：低有效，10k 上拉默认关 */
#define PIN_BIAS_EN_978   3   /* 同上（978 支路）*/
#define PIN_GNSS_SEL_A    6   /* U17 V1 / Q4 gate（ECO 后配对）*/
#define PIN_GNSS_SEL_B    7   /* U17 V2 / Q5 gate */
#define PIN_ANT_SEL_1090_A 4  /* U16 SPDT V1：A=1/B=0 → J1-J3（板载 IFA）；
                               * A=0/B=1 → J1-J2（外接 J6）。默认装配，
                               * 真值表与 GNSS 开关一致（netlist U8.6/U8.7）*/
#define PIN_ANT_SEL_1090_B 5  /* U16 SPDT V2（netlist U8.7）*/
#define PIN_SUBG_SCK      10  /* CC1312R SPI1 —— WP-E 启用前不动 */
#define PIN_SUBG_MOSI     11
#define PIN_SUBG_MISO     12
#define PIN_SUBG_CSN      13
#define PIN_SUBG_IRQ      14
#define PIN_SUBG_SYNC     15
/* CC1312R 的 RESET_N（低有效，板上 R47 10k 上拉）。同一个脚此前在
 * spi_master.c 与 cjtag.h 各有一份本地 #define——新代码一律用这个名字。 */
#define PIN_SUBG_RESET    18
#define PIN_PULSES        19  /* TLV3501 → PIO 上升沿捕获 */
#define PIN_SELFTEST_OUT  24  /* 自检脉冲输出；跳线 24→19 前**先拆下 R57**
                               * （33Ω，TLV3501 输出→PULSES 的串阻：33Ω
                               * 对 1k 串阻分支约 30:1 占优，不拆则节点
                               * 跟随比较器——"串 ≥1k 电平胜出"物理不
                               * 成立，见 selftest_gen.h；拆后直连即可）。
                               * audit P1-4：原 18 是 SUBG_RESET（CC1312R），
                               * PINMAP §2 严禁挪用；24 = RECOVERED_CLK，
                               * 调试网络，空置可安全借用。落点：v4 生产板
                               * TP7 存在（kicad_pcb:38901，audit round 4
                               * 勘误；PINMAP.md:41 的"V4 已删 TP7"与 PCB
                               * 不符，归硬件侧勘误），v3 亦有 TP7 */
#define PIN_TL_PWM        25  /* 门限 PWM → R34/C49（RC≈1ms，F5）→ LEVEL_BIAS */
#define PIN_ADC_LEVEL     26  /* ADC0：门限直流回读 */
#define PIN_ADC_RSSI      27  /* ADC1：AD8313 RSSI */
/* ADC2：USB_VBUS_SENSE 分压中点（PCB 焊盘已核：U8 pad 40 → USB_VBUS_SENSE，
 * pad 39 = RSSI = GPIO27，故 pad 40 = GPIO28）。
 * ⚠ 分压比**随板型不同**：V4 = 30k/10k（4.0），V3 = 10k/10k（2.0）。
 * RP2040 是两块板共用的**单一构建**、没有板型检测，所以本侧只上报**分压
 * 中点的电压**，换算成 VBUS 由 P4 做——那边有 Kconfig 驱动的
 * pk_board_profile()。把比例放这边就得先发明一套板型检测，猜错是静默的
 * 2 倍误差（PLAN.md F6）。 */
#define PIN_ADC_VBUS      28

/* F2 默认 GNSS 天线选择：A=0/B=1 → J1-J2（外接）导通且其 bias 路径
 * 被选中（ECO 后选择线即馈电使能，PLAN.md §3.1 F2）。台架默认外接。 */
#define RF_SAFETY_DEFAULT_GNSS_A 0
#define RF_SAFETY_DEFAULT_GNSS_B 1
